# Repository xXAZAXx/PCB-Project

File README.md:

# Kicad PCB Project
*Group 10*

Group 10 PCB Project - Power Electronics 1

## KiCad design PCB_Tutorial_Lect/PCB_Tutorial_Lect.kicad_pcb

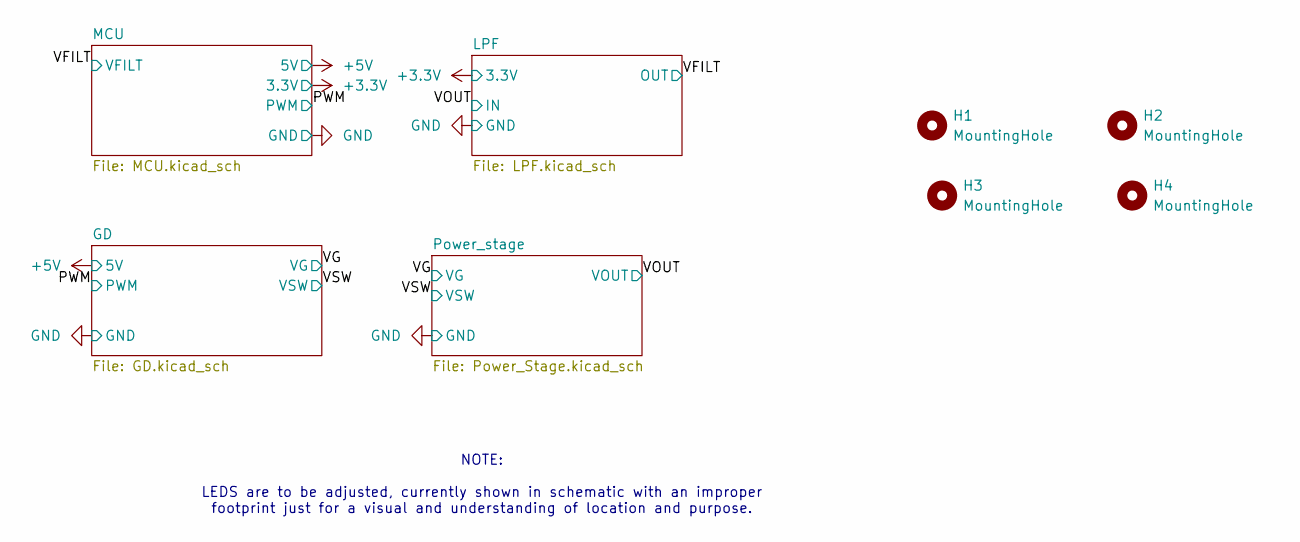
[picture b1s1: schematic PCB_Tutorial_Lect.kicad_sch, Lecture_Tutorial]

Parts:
H1, H2, H3, H4: MountingHole; MountingHole_4mm; Part No. 971100244

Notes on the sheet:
NOTE: LEDS are to be adjusted, currently shown in schematic with an improper footprint just for a visual and understanding of location and purpose.

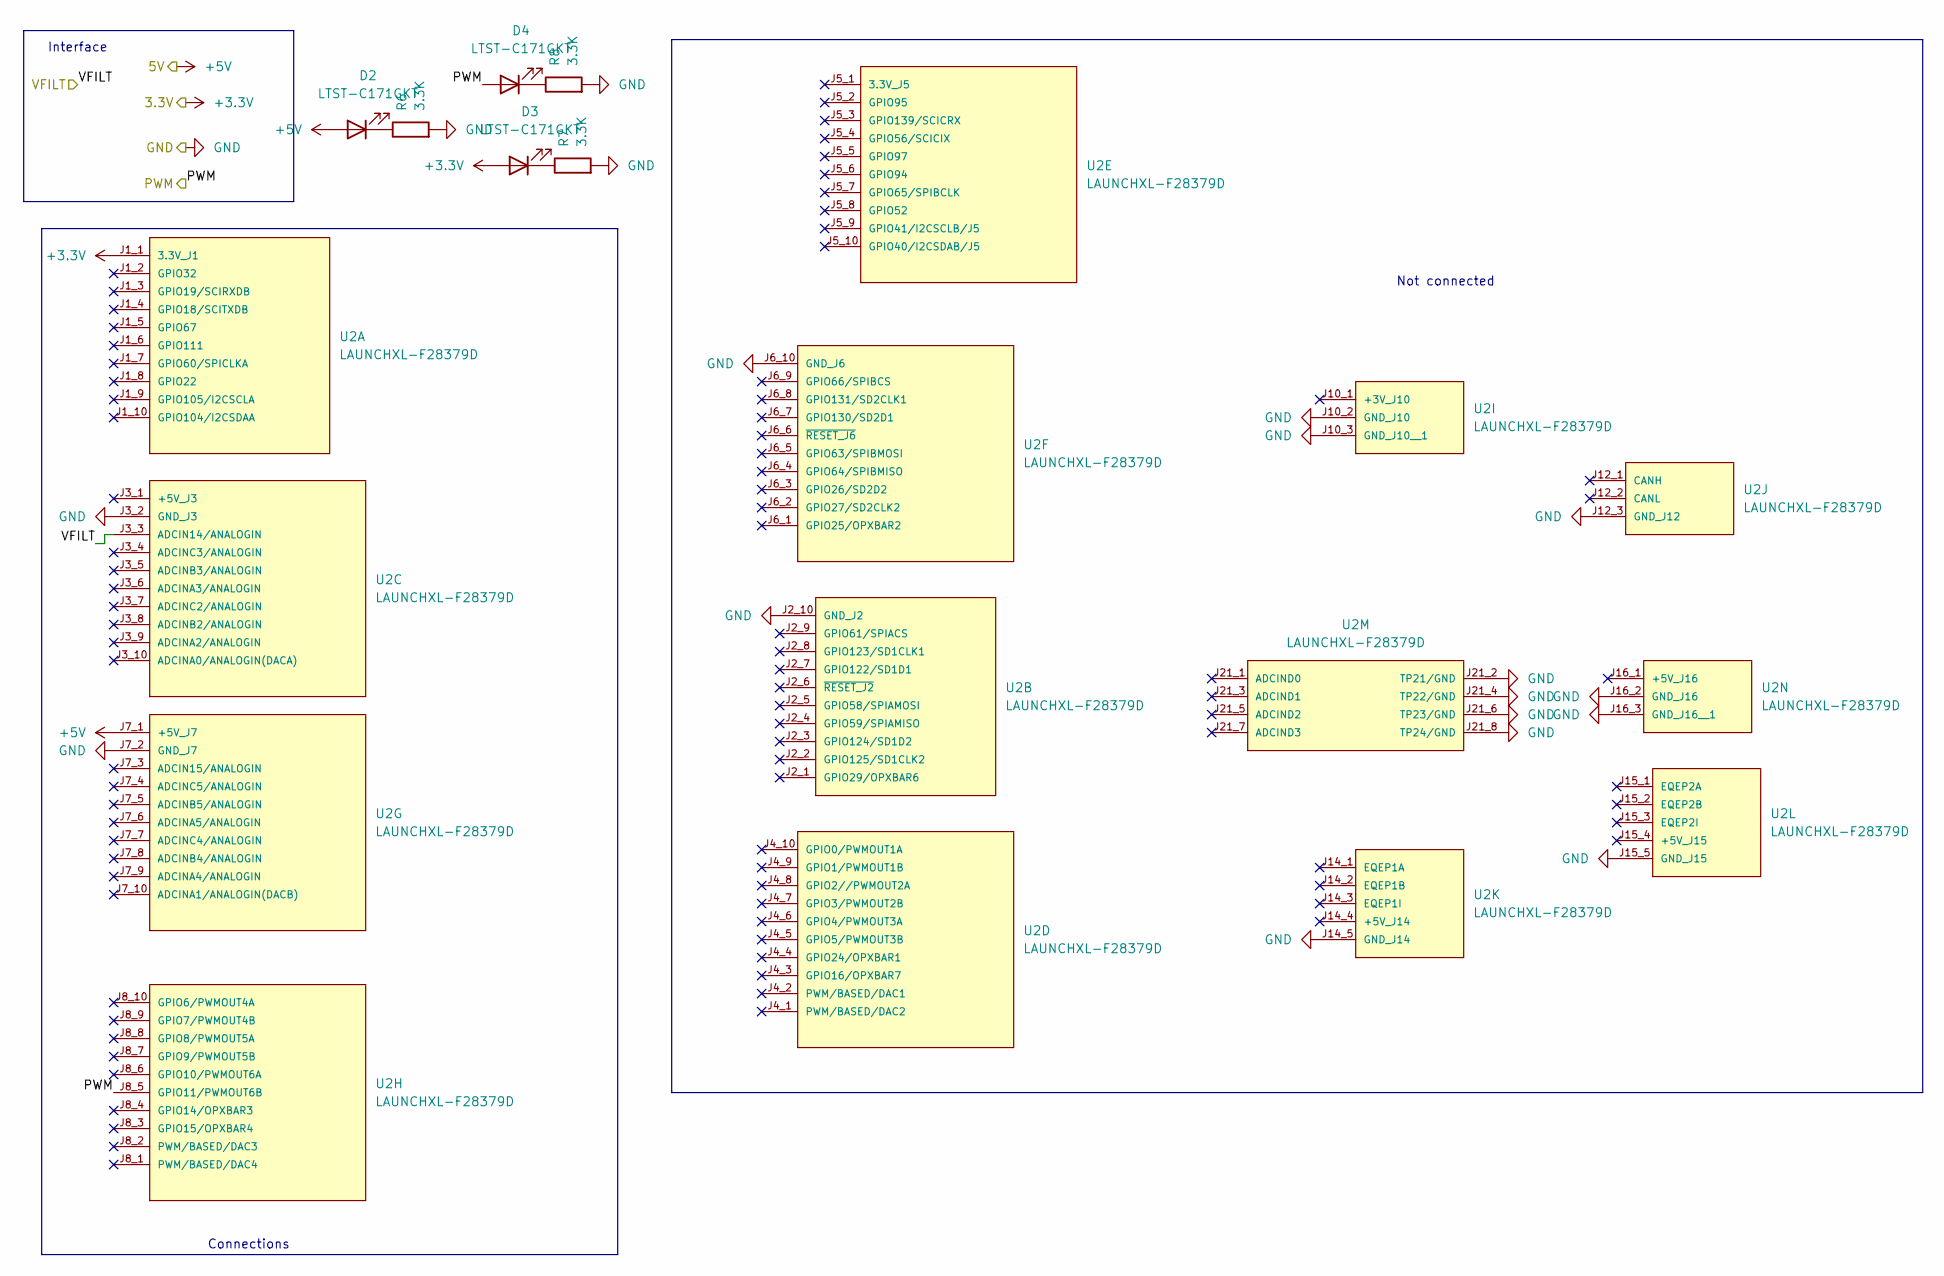
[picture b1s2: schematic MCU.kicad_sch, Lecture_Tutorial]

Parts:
D2, D3, D4: LTST-C171GKT; LED_0805_2012Metric; Part No. LTST-C171GKT
R6, R7, R8: 3.3K; R_0805_2012Metric_Pad1.20x1.40mm_HandSolder; Part No. ERJ-P06F3301V
U2: LAUNCHXL-F28379D; MOD_LAUNCHXL-F28379D; PARTREV 2.0

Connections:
+3.3V: D3.2 (A), U2.J1_1 (3.3V_J1); also elsewhere on the board
+5V: D2.2 (A), U2.J7_1 (+5V_J7); also elsewhere on the board
/PWM: D4.2 (A), U2.J8_5 (GPIO11/PWMOUT6B); also elsewhere on the board
/VFILT: U2.J3_3 (ADCIN14/ANALOGIN); also elsewhere on the board
GND: R6.2, R7.2, R8.2, U2.J2_10 (GND_J2), U2.J3_2 (GND_J3), U2.J6_10 (GND_J6), U2.J7_2 (GND_J7), U2.J10_2 (GND_J10), U2.J10_3 (GND_J10__1), U2.J12_3 (GND_J12), U2.J14_5 (GND_J14), U2.J15_5 (GND_J15), U2.J16_2 (GND_J16), U2.J16_3 (GND_J16__1), U2.J21_2 (TP21/GND), U2.J21_4 (TP22/GND), U2.J21_6 (TP23/GND), U2.J21_8 (TP24/GND); also elsewhere on the board
unnamed: D2.1 (K), R6.1
unnamed: D3.1 (K), R7.1
unnamed: D4.1 (K), R8.1

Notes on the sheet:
Interface
Not connected
Connections

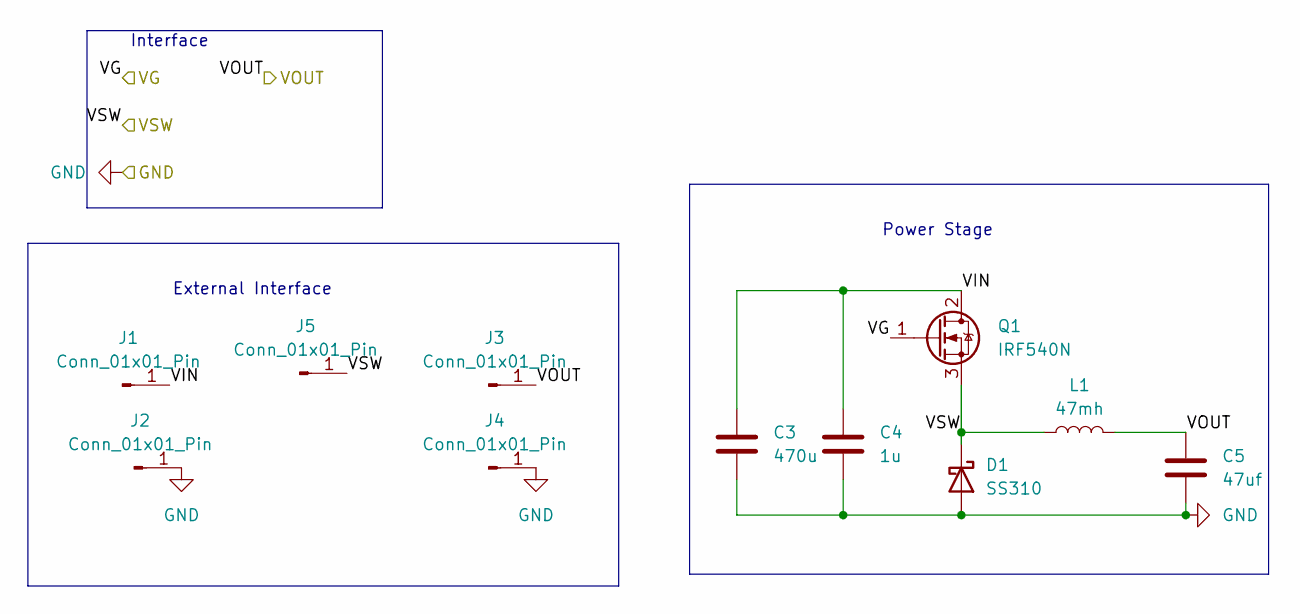
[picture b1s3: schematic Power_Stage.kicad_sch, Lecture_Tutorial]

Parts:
C3: 470u; CP_Radial_D18.0mm_P7.50mm; Part No. 100ZLH470MEFC16X31.5
C4: 1u; C_0805_2012Metric; Part No. T58W9105M035C0500
C5: 47uf; CP_Radial_D18.0mm_P7.50mm; Part No. EEU-FR1J470
D1: SS310; D_SMA; Part No. SS310
J1, J2, J3, J4, J5: Conn_01x01_Pin; Banana_Jack_1Pin; Part No. BU-P72930-2
L1: 47mh; 5500R-566K_API; Part No. 5500R-566K
Q1: IRF540N; TO-220-3_Vertical; Part No. IRF540N

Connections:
/Power_stage/VIN: C3.1, C4.1, J1.1, Q1.2 (D)
/VG: Q1.1 (G); also elsewhere on the board
/VOUT: C5.1, J3.1, L1.2; also elsewhere on the board
/VSW: D1.1 (K), J5.1, L1.1, Q1.3 (S); also elsewhere on the board
GND: C3.2, C4.2, C5.2, D1.2 (A), J2.1, J4.1; also elsewhere on the board

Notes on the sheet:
Power Stage
Interface
External Interface

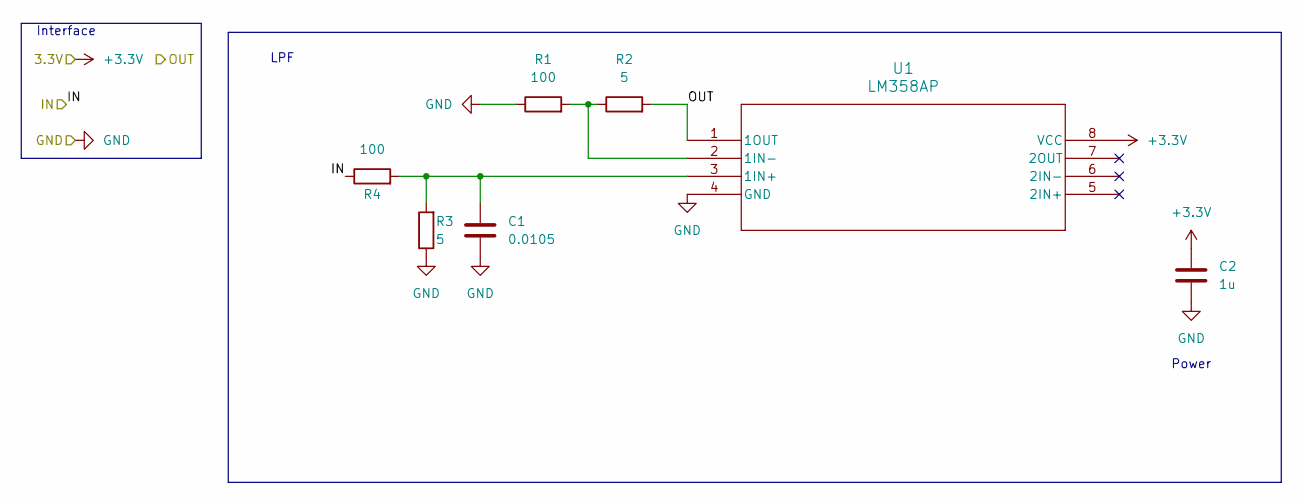
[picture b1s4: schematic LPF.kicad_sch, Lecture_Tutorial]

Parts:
C1: 0.0105; C_0805_2012Metric; Part No. SLPX153M025A9P3
C2: 1u; C_0805_2012Metric; Part No. T58W9105M035C0500
R1, R4: 100; R_0805_2012Metric; Part No. RC0805FR-07100RL
R2, R3: 5; R_0805_2012Metric; Part No. RLT1220-F-5R00-FNH
U1: LM358AP; P8; Part No. LM358AP

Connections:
+3.3V: C2.1, U1.8 (VCC); also elsewhere on the board
/VFILT: R2.2, U1.1 (1OUT); also elsewhere on the board
/VOUT: R4.1; also elsewhere on the board
GND: C1.2, C2.2, R1.1, R3.1, U1.4 (GND); also elsewhere on the board
unnamed: C1.1, R3.2, R4.2, U1.3 (1IN+)
unnamed: R1.2, R2.1, U1.2 (1IN-)

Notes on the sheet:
Interface
Power
LPF

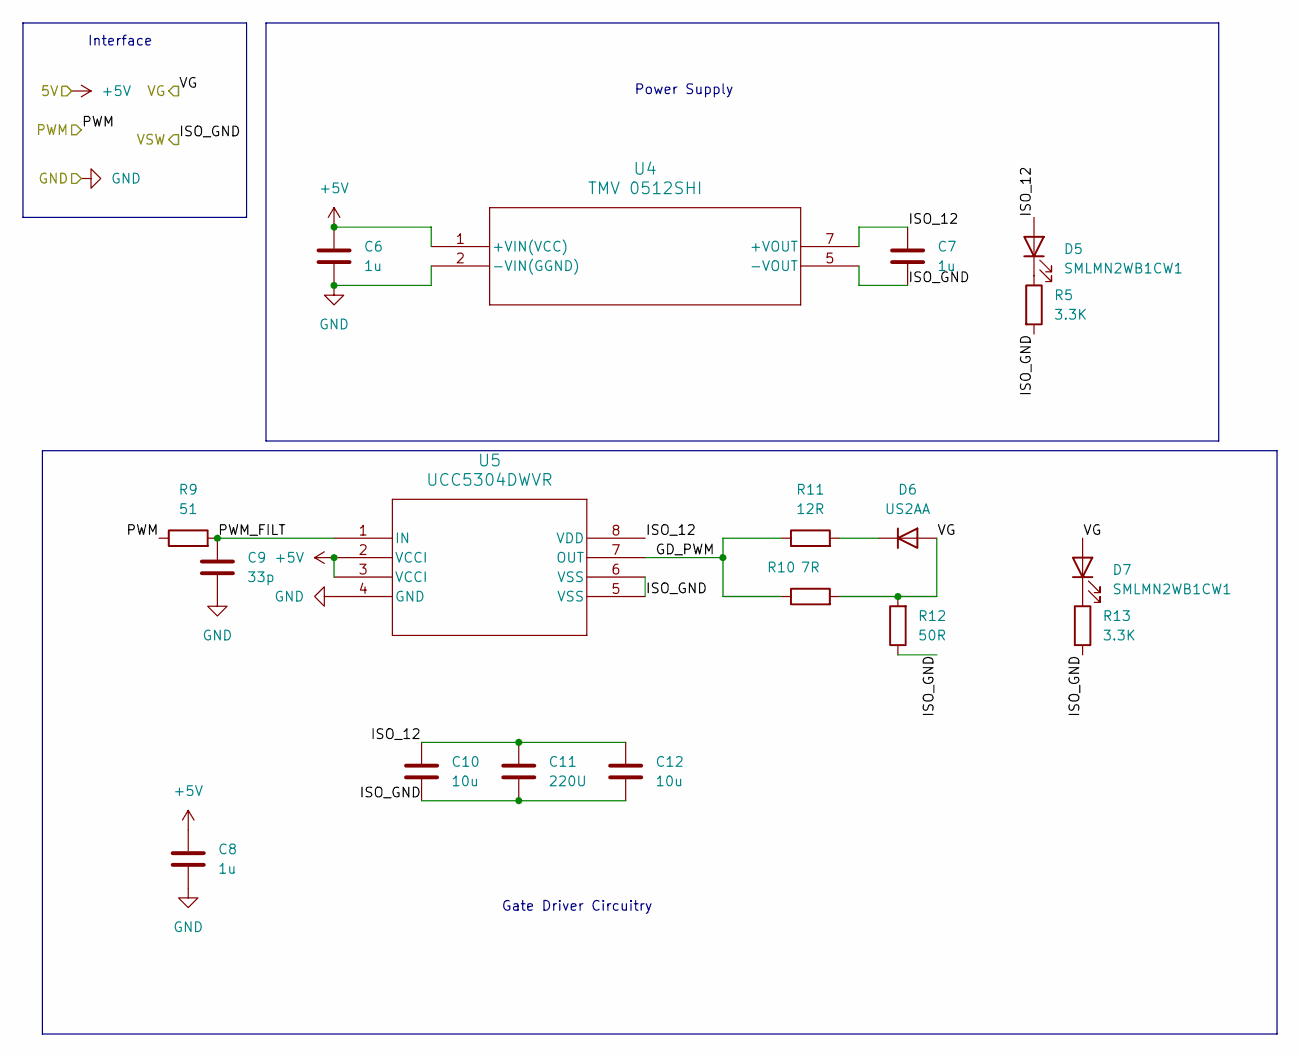
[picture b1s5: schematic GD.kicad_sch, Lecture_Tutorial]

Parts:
C6, C7: 1u; C_0805_2012Metric; Part No. T58W9105M035C0500
C8: 1u; C_0805_2012Metric_Pad1.18x1.45mm_HandSolder; Part No. T58W9105M035C0500
C9: 33p; C_0805_2012Metric_Pad1.18x1.45mm_HandSolder; Part No. 600F330FT250XT4K
C10, C12: 10u; C_0805_2012Metric; Part No. TAJP106M010RNJ
C11: 220U; C_0805_2012Metric; Part No. 298D227X0004P2T
D5, D7: SMLMN2WB1CW1; LED_0805_2012Metric; Part No. SMLMN2WB1CW1
D6: US2AA; D_SMA; Part No. US2AA
R5, R13: 3.3K; R_0805_2012Metric_Pad1.20x1.40mm_HandSolder; Part No. ERJ-P06F3301V
R9: 51; R_0805_2012Metric_Pad1.20x1.40mm_HandSolder; Part No. RC0805FR-0751RL
R10: 7R; R_0805_2012Metric_Pad1.20x1.40mm_HandSolder; Part No. RMCF0805FT10K0
R11: 12R; R_0805_2012Metric_Pad1.20x1.40mm_HandSolder; Part No. RC0805FR-0713RL
R12: 50R; R_1206_3216Metric_Pad1.30x1.75mm_HandSolder; Part No. RCP1206W50R0JTP
U4: TMV 0512SHI; TMV-HI_SINGLE_TRP; Part No. TMV 0512SHI
U5: UCC5304DWVR; SOIC8_DWV_TEX; Part No. UCC5304DWVR

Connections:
+5V: C6.1, C8.1, U4.1 (+VIN(VCC)), U5.2 (VCCI), U5.3 (VCCI); also elsewhere on the board
/GD/GD_PWM: R10.1, R11.1, U5.7 (OUT)
/GD/ISO_12: C7.1, C10.1, C11.1, C12.1, D5.2 (A), U4.7 (+VOUT), U5.8 (VDD)
/GD/PWM_FILT: C9.1, R9.2, U5.1 (IN)
/PWM: R9.1; also elsewhere on the board
/VG: D6.2 (A), D7.2 (A), R10.2, R12.2; also elsewhere on the board
/VSW: C7.2, C10.2, C11.2, C12.2, R5.2, R12.1, R13.2, U4.5 (-VOUT), U5.5 (VSS), U5.6 (VSS); also elsewhere on the board
GND: C6.2, C8.2, C9.2, U4.2 (-VIN(GGND)), U5.4 (GND); also elsewhere on the board
unnamed: D5.1 (K), R5.1
unnamed: D6.1 (K), R11.2
unnamed: D7.1 (K), R13.1

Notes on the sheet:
Interface
Power Supply
Gate Driver Circuitry

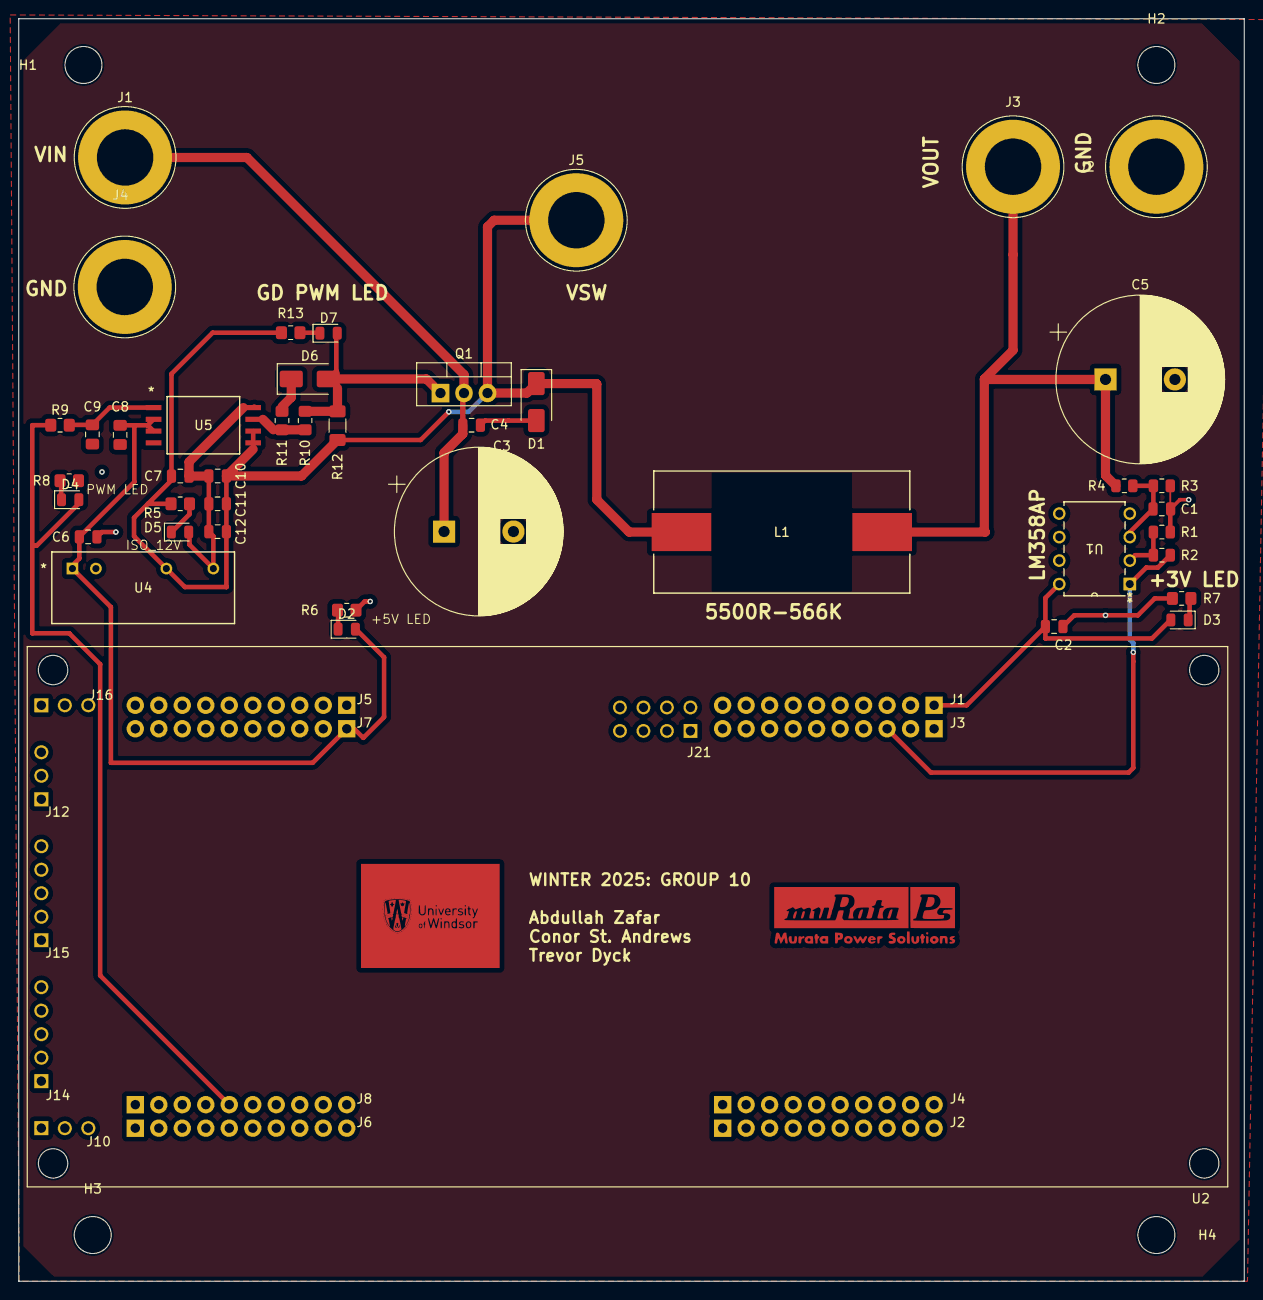
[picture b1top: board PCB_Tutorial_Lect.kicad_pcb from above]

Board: 2 copper layers, 132.5 x 136.5 mm, 47 parts (0 on the bottom side), 20 nets.
